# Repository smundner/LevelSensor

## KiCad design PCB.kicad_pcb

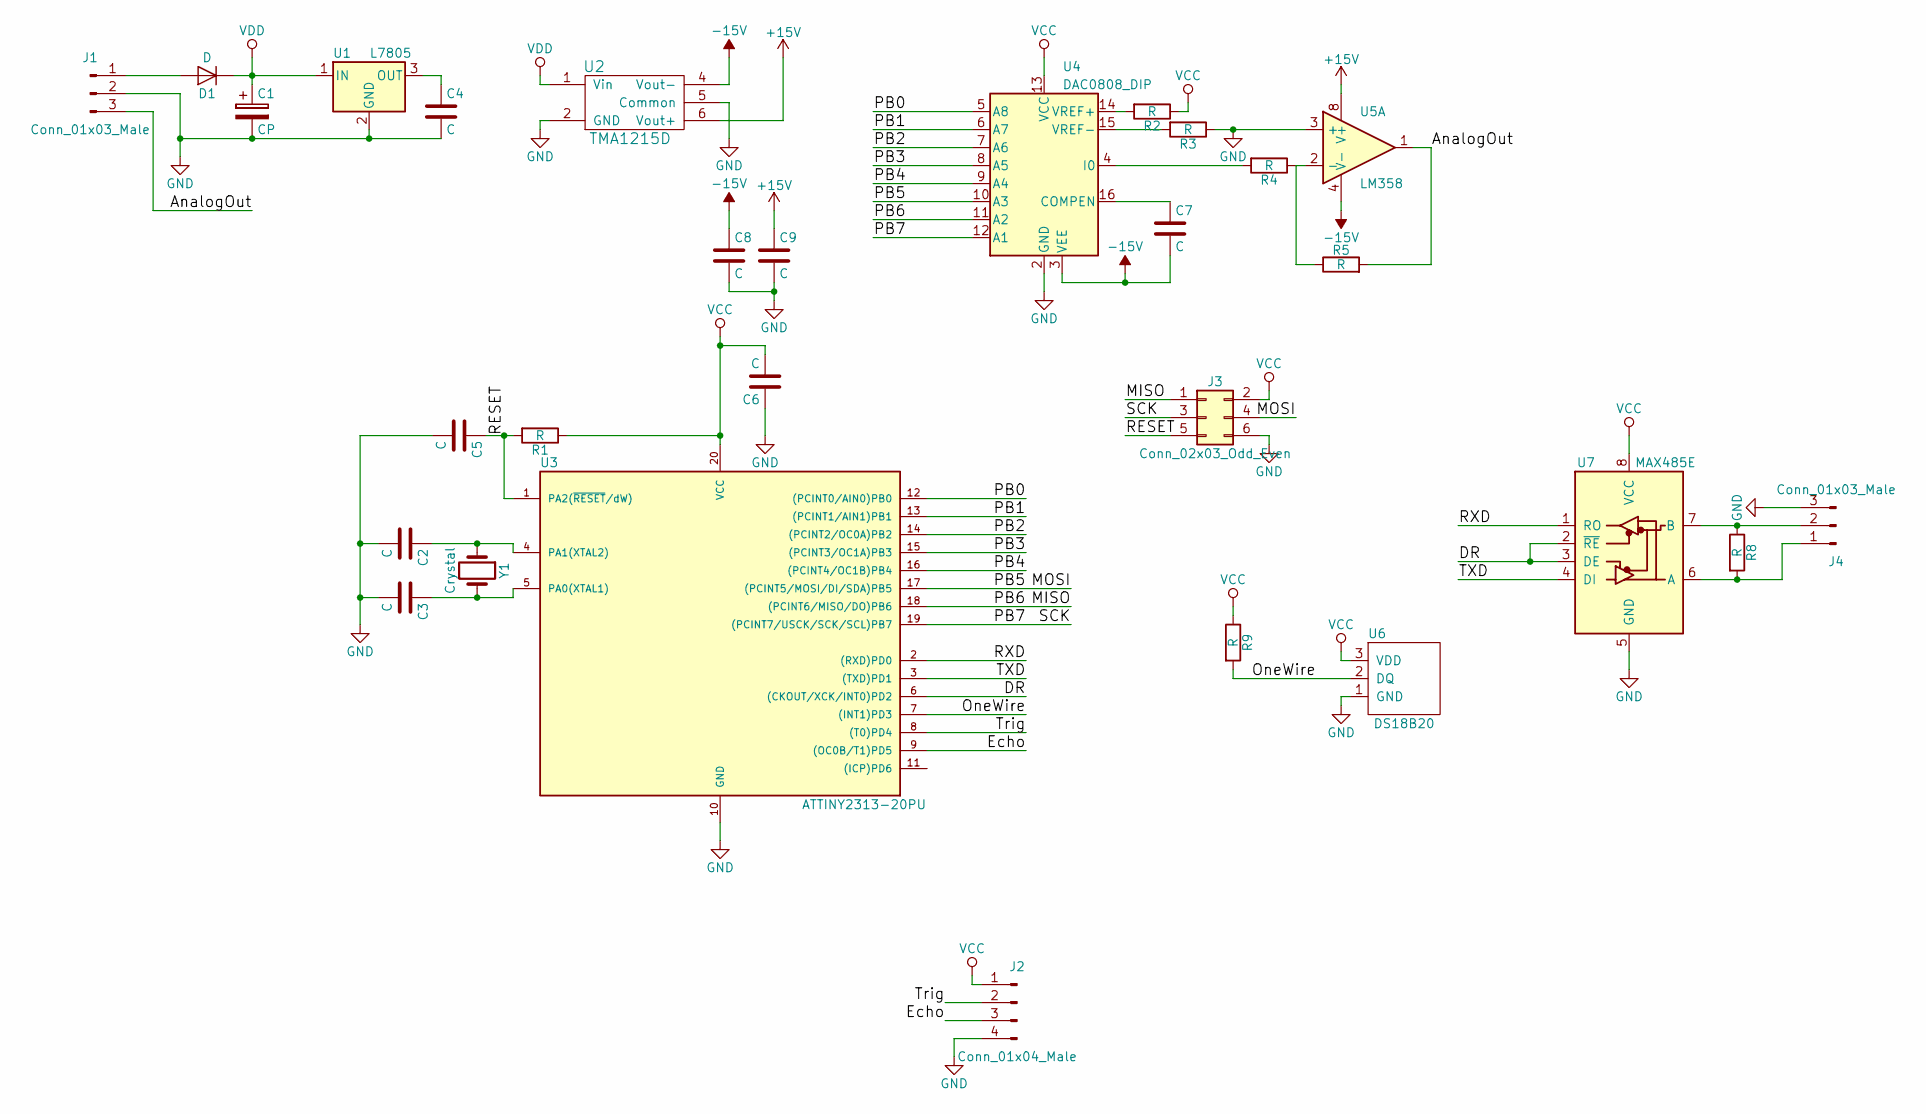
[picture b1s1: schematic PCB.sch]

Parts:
C1: CP; CP_Radial_D5.0mm_P2.00mm
C2, C3: C; C_Disc_D4.3mm_W1.9mm_P5.00mm
C4, C5, C6, C7, C8, C9: C; C_Disc_D3.8mm_W2.6mm_P2.50mm
D1: D; D3
J1, J4: Conn_01x03_Male; Fan_Pin_Header_Straight_1x03
J2: Conn_01x04_Male; JST_EH_B04B-EH-A_04x2.50mm_Straight
J3: Conn_02x03_Odd_Even; IDC_Header_Straight_6pins
R1, R2, R3, R4, R5, R8, R9: R; R_Axial_DIN0207_L6.3mm_D2.5mm_P7.62mm_Horizontal
U1: L7805; TO-220-3_Horizontal
U2: TMA1215D; DCDC-Conv_TRACO_TMH-xxxx_Dual_RevB
U3: ATTINY2313-20PU; DIP-20_W7.62mm
U4: DAC0808_DIP; DIP-16_W7.62mm
U5: LM358; DIP-8_W7.62mm
U6: DS18B20; TO-92_Inline_Narrow_Oval
U7: MAX485E; DIP-8_W7.62mm
Y1: Crystal; Crystal_HC49-U_Vertical

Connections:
+15V: C9.1, U2.6 (Vout+), U5.8 (V+)
-15V: C7.2, C8.1, U2.4 (Vout-), U4.3 (VEE), U5.4 (V-)
/AnalogOut: J1.3, R5.2, U5.1
/DR: U3.6 ((CKOUT/XCK/INT0)PD2), U7.2 (~RE), U7.3 (DE)
/Echo: J2.3, U3.9 ((OC0B/T1)PD5)
/MISO: J3.1, U3.18 ((PCINT6/MISO/DO)PB6), U4.11 (A2)
/MOSI: J3.4, U3.17 ((PCINT5/MOSI/DI/SDA)PB5), U4.10 (A3)
/OneWire: R9.2, U3.7 ((INT1)PD3), U6.2 (DQ)
/PB0: U3.12 ((PCINT0/AIN0)PB0), U4.5 (A8)
/PB1: U3.13 ((PCINT1/AIN1)PB1), U4.6 (A7)
/PB2: U3.14 ((PCINT2/OC0A)PB2), U4.7 (A6)
/PB3: U3.15 ((PCINT3/OC1A)PB3), U4.8 (A5)
/PB4: U3.16 ((PCINT4/OC1B)PB4), U4.9 (A4)
/PB7: J3.3, U3.19 ((PCINT7/USCK/SCK/SCL)PB7), U4.12 (A1)
/RESET: C5.1, J3.5, R1.2, U3.1 (PA2(~RESET~/dW))
/RXD: U3.2 ((RXD)PD0), U7.1 (RO)
/TXD: U3.3 ((TXD)PD1), U7.4 (DI)
/Trig: J2.2, U3.8 ((T0)PD4)
GND: C1.2, C2.2, C3.2, C4.2, C5.2, C6.1, C8.2, C9.2, J1.2, J2.4, J3.6, J4.3, R3.1, U1.2 (GND), U2.2 (GND), U2.5 (Common), U3.10 (GND), U4.2 (GND), U5.3 (+), U6.1 (GND), U7.5 (GND)
unnamed: C2.1, U3.4 (PA1(XTAL2)), Y1.1
unnamed: C3.1, U3.5 (PA0(XTAL1)), Y1.2
unnamed: C4.1, U1.3 (OUT)
unnamed: C7.1, U4.16 (COMPEN)
unnamed: D1.2 (A), J1.1
unnamed: J4.1, R8.2, U7.6 (A)
unnamed: J4.2, R8.1, U7.7 (B)
unnamed: R2.2, U4.14 (VREF+)
unnamed: R3.2, U4.15 (VREF-)
unnamed: R4.1, R5.1, U5.2 (-)
unnamed: R4.2, U4.4 (I0)
VCC: C6.2, J2.1, J3.2, R1.1, R2.1, R9.1, U3.20 (VCC), U4.13 (VCC), U6.3 (VDD), U7.8 (VCC)
VDD: C1.1, D1.1 (K), U1.1 (IN), U2.1 (Vin)

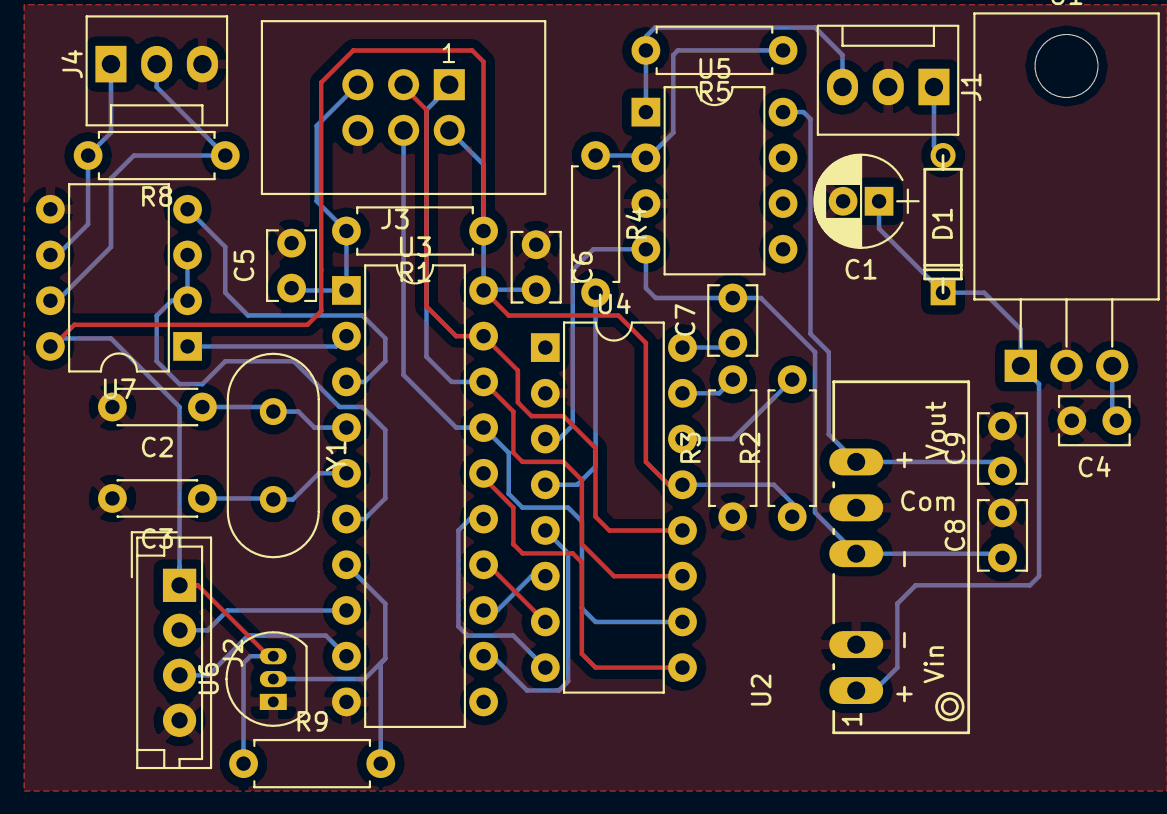
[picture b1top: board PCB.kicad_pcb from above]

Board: 2 copper layers, 29 parts (0 on the bottom side), 32 nets.

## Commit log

2018-01-14 PCB erstellt
2018-01-14 Createbox
2018-01-14 add program basics
2018-02-03 add box
2018-02-21 add Program
    add timer function
    add RS485 function
    add ds18x20 function
    add hc-sr04
2018-02-27 Makefile modifiziert
2018-02-27 aufgeraumt
